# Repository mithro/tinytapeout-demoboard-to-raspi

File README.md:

# Raspmod: TinyTapeout demoboard to Raspberry Pi

Connects all I/O from TT demoboard to RPi ribbon cable while still allowing the PMODs to be used with external modules.

Simple two layer board, everything but the 100 mil headers is pretty much optional.

Only annoying bit is that the clock and reset are only available through the SIL (not one of the PMODs) so these must be connected by adding a 2-pin header to the demoboard in the right spot.

## Direct variant: on the Pi's GPIO header, flat beside the FPGA board

This branch (`direct-gpio`) is the same board altered to do without the
ribbon. It sits **on** a Raspberry Pi's 40-pin header, and lies flat beside
a Tiny Tapeout demoboard or a Digilent Arty, plugging into their Pmod
hosts sideways.

What changed, and why:

- **J1** is a low-profile SMT socket on the underside -- Adafruit 2187,
  Kaweei CS25582-40G-M36-0A, 3.8 mm tall -- so the board sits straight on
  the Pi's header. The socket's own drawing has the pins pass through the
  PCB, so the forty plated holes stay as they were and forty SMT pads join
  them, each linked to its hole on the back. The pads are the middle 1.5 mm
  of the 2.1 mm the drawing shows: the full pad would stop 0.33 mm from the
  board edge, and the ground pour needs the room between the holes and the
  pads.
- **J2, J3, J4**, the straight plugs on the underside that went into a
  demoboard's hosts while the board stood on edge, are right-angle 2x6
  headers on the component side, pins out past the edge (Wurth 61301221021
  or the like). Same pads, same numbers, same nets; the footprint is the
  Tiny Tapeout library's right-angle one mirrored, since the library's
  numbering would put pin 1 at the other end.
- **10 mm shorter** at the pin-40 end. Sat on the Pi, that end reached
  over the Pi's Ethernet or USB stack, 13.5 to 16 mm tall, which a board
  6.3 mm up cannot clear. J10 (the auxiliary socket) and SW1 (the user
  button, with R1, R2 and C1) were there; they go. **J9**, the clock/reset
  socket on the underside, goes too: it dropped onto the demoboard's pins
  from above and cannot reach them from beside it. J8 on top stays, for a
  flying lead.
- **J1 pin 17**, the Pi's second 3V3 pin, is not connected; pin 1 feeds
  the 3V3 rail. The rail ran on the back along the top edge, where the
  socket's outer row of pads now is, so it moved to the front along the
  edge. Between it and the pin row is a strip of ground pour, and that
  strip is the only way out for the ground pins of the outer row: on the
  back each of them is boxed in by the signal pads either side. A stub from
  pin 17 up to the rail would cut the strip and box pin 9 in. The Pi's two
  3V3 pins are one rail, and the socket contact is rated 3 A against three
  Pmods' 100 mA each.
- **Fits a Raspberry Pi 5 or 3B.** Not a 3B+ or 4B: their PoE header
  stands 8.5 mm tall 0.4 mm from pin 39's pad, under a board that sits
  2.54 + 3.8 = 6.34 mm up.

Heights, for anyone mounting the pair: the board's underside is 6.34 mm
above the Pi's top face and its top 7.94; its plug rows are then 1.27 and
3.81 mm above that, and a standard right-angle Pmod host socket has its
rows 4.53 and 7.07 mm above its own board, so the FPGA board's top face
sits **4.68 mm above the Pi's**. The mechanical drawings of this board and
of two base plates that hold it with a Pi and a demoboard or an Arty are
in [fpgas.online-mechanical](https://github.com/fpgas-online/fpgas.online-mechanical)
(`ACC-HAT-DRMOD`, `BP-TT`, `BP-ARTY`).

### Reproducing the change

The files are KiCad 10's, and everything below runs KiCad 10 in its own
Docker image (`scripts/kicad10.sh`). The edit itself is a script over
upstream's board and schematic, so the diff can be read as a program:

```sh
git checkout 0dae4bf -- TTDB_2_Raspi.kicad_pcb TTDB_2_Raspi.kicad_sch
mkdir -p tmp && cp TTDB_2_Raspi.kicad_pcb tmp/upstream.kicad_pcb
scripts/kicad10.sh build      # make_direct.py, fill, restitch.py, fill
scripts/kicad10.sh verify     # every kept pad where it was, on its net
scripts/kicad10.sh check      # DRC with schematic parity, and ERC
scripts/kicad10.sh images     # the renders above
```

`verify` proves, under KiCad's own Python, that every part kept has every
pad where upstream had it with its number and its net, that pin 17 is the
one deliberate change of net, that J1's forty SMT pads sit beside their
holes on the same nets, and that the outline is 10 mm shorter on the left
and nothing else. `check` reports no unconnected items and no parity
issues; what it does report is the same class of silkscreen warning and
library notice the untouched original reports, fewer of them.

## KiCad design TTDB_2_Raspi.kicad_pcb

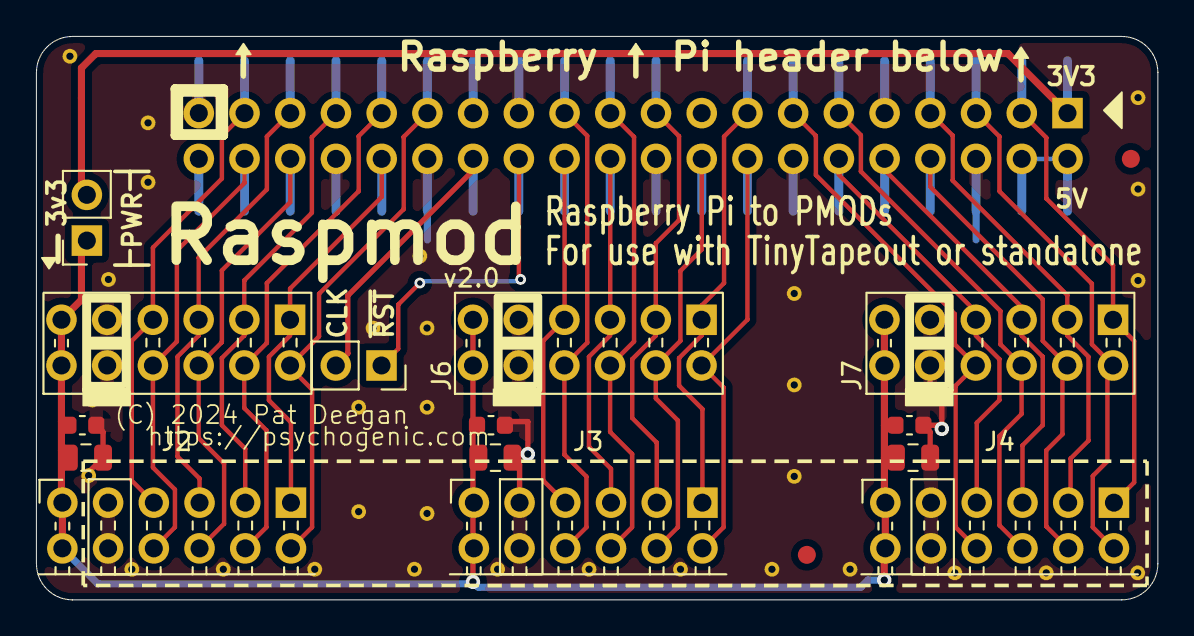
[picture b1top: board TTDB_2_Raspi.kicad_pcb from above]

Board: 2 copper layers, 62.3 x 31.3 mm, 48 parts (0 on the bottom side), 30 nets.

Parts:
C2, C4, C6: C_10u_0805_35V; C_0805_2012Metric
C3, C5, C7: C_1u_0603_50V; C_0603_1608Metric
FID1, FID2: Fiducial; Fiducial_1mm_Mask2mm
J1: CS25582-40G-M36-0A; PinSocket_2x20_P2.54mm_SMD_CS25582_Under
J2, J3, J4: 61301221021; PinHeader_2x06_P2.54mm_PMODPeriph2B_TopRA_Mirror
J5, J6, J7: 613012243121; PinSocket_2x06_P2.54mm_PMODHost1A_VERT
J8, J11: Conn_01x02; PinSocket_1x02_P2.54mm_Vertical
STITCH1, STITCH2, STITCH3, STITCH4, STITCH5, STITCH6, STITCH7, STITCH8, STITCH9, STITCH10, STITCH11, STITCH12, STITCH14, STITCH21, STITCH26, STITCH27, STITCH28, STITCH29, STITCH30, STITCH31, STITCH31#2, STITCH31#3, STITCH31#4, STITCH31#5, STITCH31#6, STITCH31#7, STITCH31#8, STITCH31#9, STITCH31#10, STITCH31#11, STITCH31#12: StitchingVia-0.4mmDrill

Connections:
+3V3: C2.1, C3.1, C4.1, C5.1, C6.1, C7.1, J2.6 (VCC), J2.12 (VCC), J3.6 (VCC), J3.12 (VCC), J4.6 (VCC), J4.12 (VCC), J5.6 (VCC), J5.12 (VCC), J6.6 (VCC), J6.12 (VCC), J7.6 (VCC), J7.12 (VCC), J11.1
/CLK: J1.28 (ID_SC_I2C0/GPIO01), J8.2
/P1_1: J1.32 (GPIO12/PWM0), J2.1 (IO1), J5.1 (IO1)
/P1_2: J1.33 (GPIO13/PWM1), J2.2 (IO2), J5.2 (IO2)
/P1_3: J1.35 (GPIO19/SPI1_MISO/PCM_FS), J2.3 (IO3), J5.3 (IO3)
/P1_4: J1.37 (GPIO26/SDIO_DAT2), J2.4 (IO4), J5.4 (IO4)
/P1_5: J1.29 (GPCLK1/GPIO05), J2.7 (IO5), J5.7 (IO5)
/P1_6: J1.31 (GPCLK2/GPIO06), J2.8 (IO6), J5.8 (IO6)
/P1_7: J1.36 (GPIO16/SPI1_~CE2), J2.9 (IO7), J5.9 (IO7)
/P1_8: J1.38 (GPIO20/SPI1_MOSI/PCM_DIN/PWM1), J2.10 (IO8), J5.10 (IO8)
/P2_1: J1.15 (GPIO22/SDIO_CLK), J3.1 (IO1), J6.1 (IO1)
/P2_2: J1.19 (MOSI_SPI0/GPIO10), J3.2 (IO2), J6.2 (IO2)
/P2_3: J1.22 (GPIO25/SDIO_DAT1), J3.3 (IO3), J6.3 (IO3)
/P2_4: J1.24 (~CE0_SPI0/GPIO08), J3.4 (IO4), J6.4 (IO4)
/P2_5: J1.16 (GPIO23/SDIO_CMD), J3.7 (IO5), J6.7 (IO5)
/P2_6: J1.18 (GPIO24/SDIO_DAT0), J3.8 (IO6), J6.8 (IO6)
/P2_7: J1.21 (MISO_SPI0/GPIO09), J3.9 (IO7), J6.9 (IO7)
/P2_8: J1.23 (SCLK_SPI0/GPIO11), J3.10 (IO8), J6.10 (IO8)
/P3_1: J1.3 (SDA_I2C1/GPIO02), J4.1 (IO1), J7.1 (IO1)
/P3_2: J1.7 (GPCLK0/GPIO04), J4.2 (IO2), J7.2 (IO2)
/P3_3: J1.10 (GPIO15/UART_RXD), J4.3 (IO3), J7.3 (IO3)
/P3_4: J1.12 (GPIO18/SPI1_~CE0/PCM_CLK/PWM0), J4.4 (IO4), J7.4 (IO4)
/P3_5: J1.5 (SCL_I2C1/GPIO03), J4.7 (IO5), J7.7 (IO5)
/P3_6: J1.8 (GPIO14/UART_TXD), J4.8 (IO6), J7.8 (IO6)
/P3_7: J1.11 (GPIO17/SPI1_~CE1), J4.9 (IO7), J7.9 (IO7)
/P3_8: J1.13 (GPIO27/SDIO_DAT3), J4.10 (IO8), J7.10 (IO8)
/~RST: J1.26 (~CE1_SPI0/GPIO07), J8.1
GND: C2.2, C3.2, C4.2, C5.2, C6.2, C7.2, J1.6 (GND), J1.9 (GND), J1.14 (GND), J1.20 (GND), J1.25 (GND), J1.30 (GND), J1.34 (GND), J1.39 (GND), J2.5 (GND), J2.11 (GND), J3.5 (GND), J3.11 (GND), J4.5 (GND), J4.11 (GND), J5.5 (GND), J5.11 (GND), J6.5 (GND), J6.11 (GND), J7.5 (GND), J7.11 (GND), STITCH1.1, STITCH2.1, STITCH3.1, STITCH4.1, STITCH5.1, STITCH6.1, STITCH7.1, STITCH8.1, STITCH9.1, STITCH10.1, STITCH11.1, STITCH12.1, STITCH14.1, STITCH21.1, STITCH26.1, STITCH27.1, STITCH28.1, STITCH29.1, STITCH30.1, STITCH31.1, STITCH31#2.1, STITCH31#3.1, STITCH31#4.1, STITCH31#5.1, STITCH31#6.1, STITCH31#7.1, STITCH31#8.1, STITCH31#9.1, STITCH31#10.1, STITCH31#11.1, STITCH31#12.1
unnamed: J1.2 (5V), J1.4 (5V)
VDD: J1.1 (3V3), J11.2

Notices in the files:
TTDB_2_Raspi.kicad_pcb:
(C) 2024 Pat Deegan
